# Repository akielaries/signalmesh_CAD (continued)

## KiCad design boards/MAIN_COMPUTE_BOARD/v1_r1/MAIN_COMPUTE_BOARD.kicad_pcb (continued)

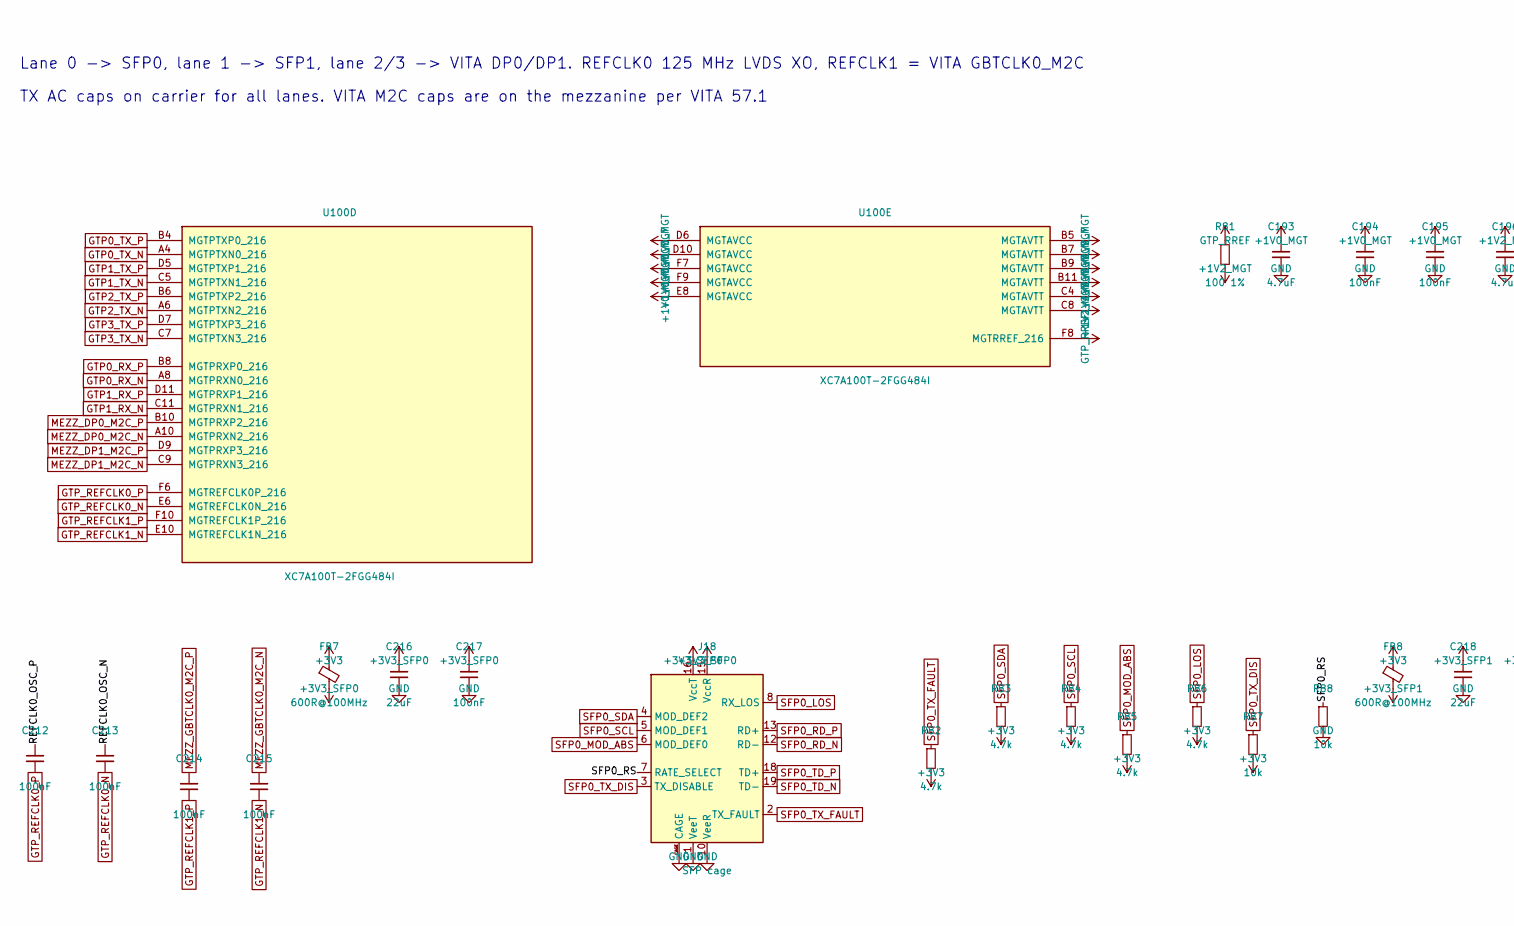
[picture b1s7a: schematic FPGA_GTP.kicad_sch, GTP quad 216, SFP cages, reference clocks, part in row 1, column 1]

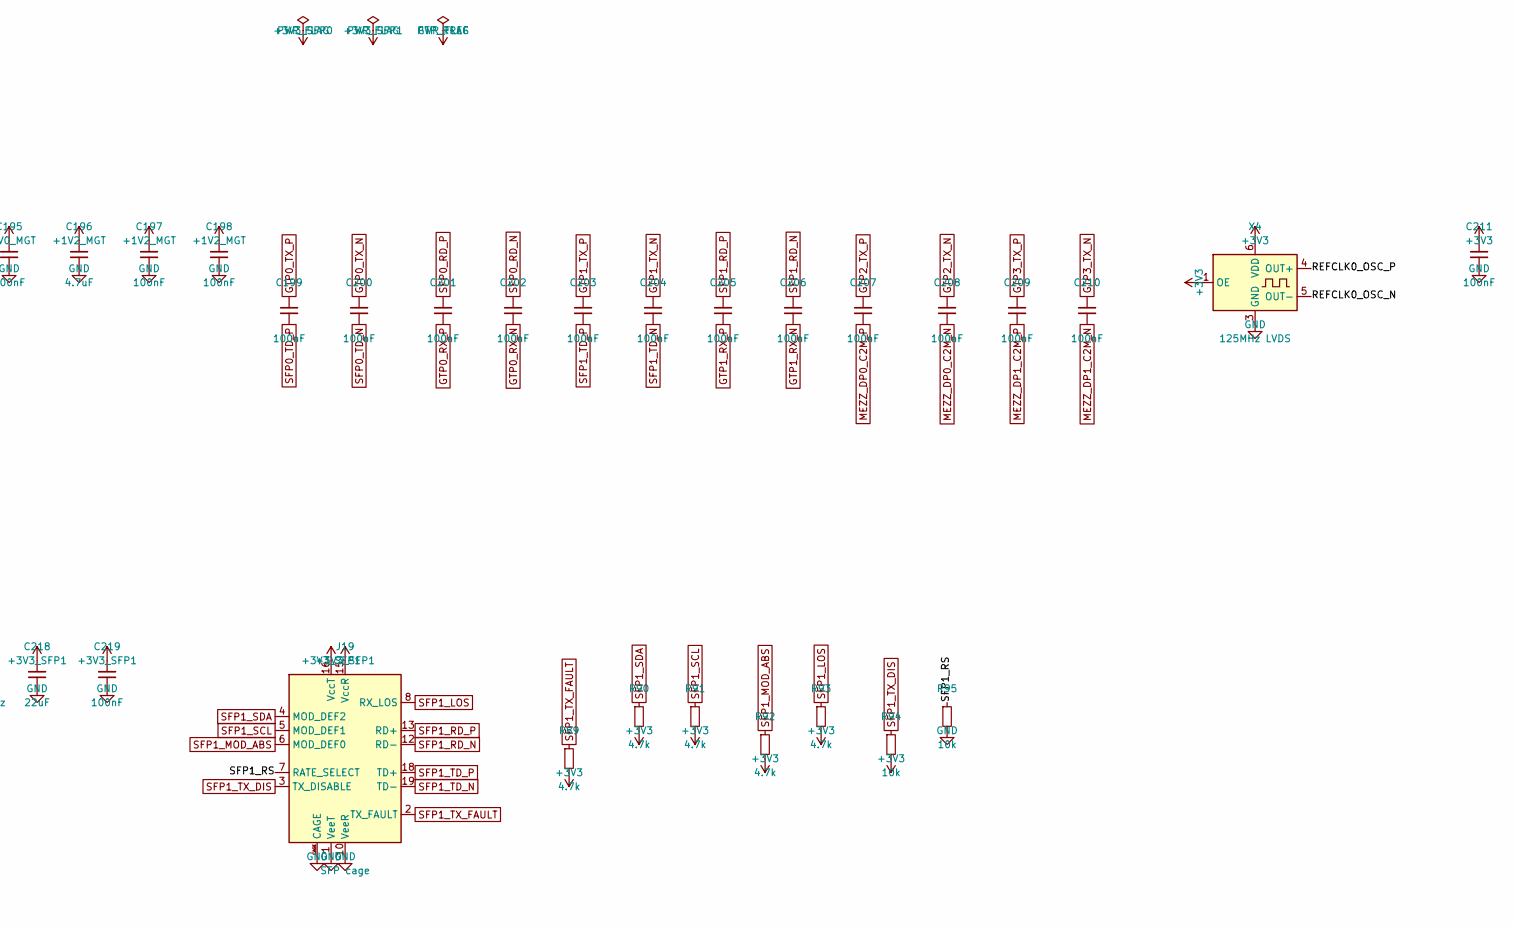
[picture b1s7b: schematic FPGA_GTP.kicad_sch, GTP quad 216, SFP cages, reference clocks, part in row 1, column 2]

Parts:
C193, C196: 4.7uF; C_0603_1608Metric
C194, C195, C197, C198, C211, C217, C219: 100nF; C_0402_1005Metric
C199, C200, C201, C202, C203, C204, C205, C206, C207, C208, C209, C210, C212, C213, C214, C215: 100nF; C_0201_0603Metric
C216, C218: 22uF; C_0805_2012Metric
FB7, FB8: 600R@100MHz; L_0603_1608Metric
J18, J19: SFP cage; Connector_SFP_and_Cage
R81: 100 1%; R_0402_1005Metric
R82, R83, R84, R85, R86, R89, R90, R91, R92, R93: 4.7k; R_0402_1005Metric
R87, R88, R94, R95: 10k; R_0402_1005Metric
U100: XC7A100T-2FGG484I; Xilinx_FGG484
X4: 125MHz LVDS; Oscillator_SMD_SiTime_PQFD-6L_3.2x2.5mm

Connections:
+1V0_MGT: C193.1, C194.1, C195.1, U100.D6 (MGTAVCC), U100.D10 (MGTAVCC), U100.E8 (MGTAVCC), U100.F7 (MGTAVCC), U100.F9 (MGTAVCC); also elsewhere on the board
+1V2_MGT: C196.1, C197.1, C198.1, R81.2, U100.B5 (MGTAVTT), U100.B7 (MGTAVTT), U100.B9 (MGTAVTT), U100.B11 (MGTAVTT), U100.C4 (MGTAVTT), U100.C8 (MGTAVTT); also elsewhere on the board
+3V3: C211.1, FB7.1, FB8.1, R82.2, R83.2, R84.2, R85.2, R86.2, R87.2, R89.2, R90.2, R91.2, R92.2, R93.2, R94.2, X4.1 (OE), X4.6 (VDD); also elsewhere on the board
+3V3_SFP0: C216.1, C217.1, FB7.2, J18.15 (VccR), J18.16 (VccT)
+3V3_SFP1: C218.1, C219.1, FB8.2, J19.15 (VccR), J19.16 (VccT)
/FPGA_GTP/REFCLK0_OSC_N: C213.1, X4.5 (OUT-)
/FPGA_GTP/REFCLK0_OSC_P: C212.1, X4.4 (OUT+)
/FPGA_GTP/SFP0_RS: J18.7 (RATE_SELECT), R88.1
/FPGA_GTP/SFP1_RS: J19.7 (RATE_SELECT), R95.1
GND: C193.2, C194.2, C195.2, C196.2, C197.2, C198.2, C211.2, C216.2, C217.2, C218.2, C219.2, J18.1 (VeeT), J18.9 (VeeR), J18.10 (VeeR), J18.11 (VeeR), J18.14 (VeeR), J18.17 (VeeT), J18.20 (VeeT), J18.CAGE, J19.1 (VeeT), J19.9 (VeeR), J19.10 (VeeR), J19.11 (VeeR), J19.14 (VeeR), J19.17 (VeeT), J19.20 (VeeT), J19.CAGE, R88.2, R95.2, X4.3 (GND); also elsewhere on the board
GTP0_RX_N: C202.2, U100.A8 (MGTPRXN0_216)
GTP0_RX_P: C201.2, U100.B8 (MGTPRXP0_216)
GTP0_TX_N: C200.1, U100.A4 (MGTPTXN0_216)
GTP0_TX_P: C199.1, U100.B4 (MGTPTXP0_216)
GTP1_RX_N: C206.2, U100.C11 (MGTPRXN1_216)
GTP1_RX_P: C205.2, U100.D11 (MGTPRXP1_216)
GTP1_TX_N: C204.1, U100.C5 (MGTPTXN1_216)
GTP1_TX_P: C203.1, U100.D5 (MGTPTXP1_216)
GTP2_TX_N: C208.1, U100.A6 (MGTPTXN2_216)
GTP2_TX_P: C207.1, U100.B6 (MGTPTXP2_216)
GTP3_TX_N: C210.1, U100.C7 (MGTPTXN3_216)
GTP3_TX_P: C209.1, U100.D7 (MGTPTXP3_216)
GTP_REFCLK0_N: C213.2, U100.E6 (MGTREFCLK0N_216)
GTP_REFCLK0_P: C212.2, U100.F6 (MGTREFCLK0P_216)
GTP_REFCLK1_N: C215.2, U100.E10 (MGTREFCLK1N_216)
GTP_REFCLK1_P: C214.2, U100.F10 (MGTREFCLK1P_216)
GTP_RREF: R81.1, U100.F8 (MGTRREF_216)
MEZZ_DP0_C2M_N: C208.2; also elsewhere on the board
MEZZ_DP0_C2M_P: C207.2; also elsewhere on the board
MEZZ_DP0_M2C_N: U100.A10 (MGTPRXN2_216); also elsewhere on the board
MEZZ_DP0_M2C_P: U100.B10 (MGTPRXP2_216); also elsewhere on the board
MEZZ_DP1_C2M_N: C210.2; also elsewhere on the board
MEZZ_DP1_C2M_P: C209.2; also elsewhere on the board
MEZZ_DP1_M2C_N: U100.C9 (MGTPRXN3_216); also elsewhere on the board
MEZZ_DP1_M2C_P: U100.D9 (MGTPRXP3_216); also elsewhere on the board
MEZZ_GBTCLK0_M2C_N: C215.1; also elsewhere on the board
MEZZ_GBTCLK0_M2C_P: C214.1; also elsewhere on the board
SFP0_LOS: J18.8 (RX_LOS), R86.1; also elsewhere on the board
SFP0_MOD_ABS: J18.6 (MOD_DEF0), R85.1; also elsewhere on the board
SFP0_RD_N: C202.1, J18.12 (RD-)
SFP0_RD_P: C201.1, J18.13 (RD+)
SFP0_SCL: J18.5 (MOD_DEF1), R84.1; also elsewhere on the board
SFP0_SDA: J18.4 (MOD_DEF2), R83.1; also elsewhere on the board
SFP0_TD_N: C200.2, J18.19 (TD-)
SFP0_TD_P: C199.2, J18.18 (TD+)
SFP0_TX_DIS: J18.3 (TX_DISABLE), R87.1; also elsewhere on the board
SFP0_TX_FAULT: J18.2 (TX_FAULT), R82.1; also elsewhere on the board
SFP1_LOS: J19.8 (RX_LOS), R93.1; also elsewhere on the board
SFP1_MOD_ABS: J19.6 (MOD_DEF0), R92.1; also elsewhere on the board
SFP1_RD_N: C206.1, J19.12 (RD-)
SFP1_RD_P: C205.1, J19.13 (RD+)
SFP1_SCL: J19.5 (MOD_DEF1), R91.1; also elsewhere on the board
SFP1_SDA: J19.4 (MOD_DEF2), R90.1; also elsewhere on the board
SFP1_TD_N: C204.2, J19.19 (TD-)
SFP1_TD_P: C203.2, J19.18 (TD+)
SFP1_TX_DIS: J19.3 (TX_DISABLE), R94.1; also elsewhere on the board
SFP1_TX_FAULT: J19.2 (TX_FAULT), R89.1; also elsewhere on the board

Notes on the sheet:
Lane 0 -> SFP0, lane 1 -> SFP1, lane 2/3 -> VITA DP0/DP1. REFCLK0 125 MHz LVDS XO, REFCLK1 = VITA GBTCLK0_M2C
TX AC caps on carrier for all lanes. VITA M2C caps are on the mezzanine per VITA 57.1

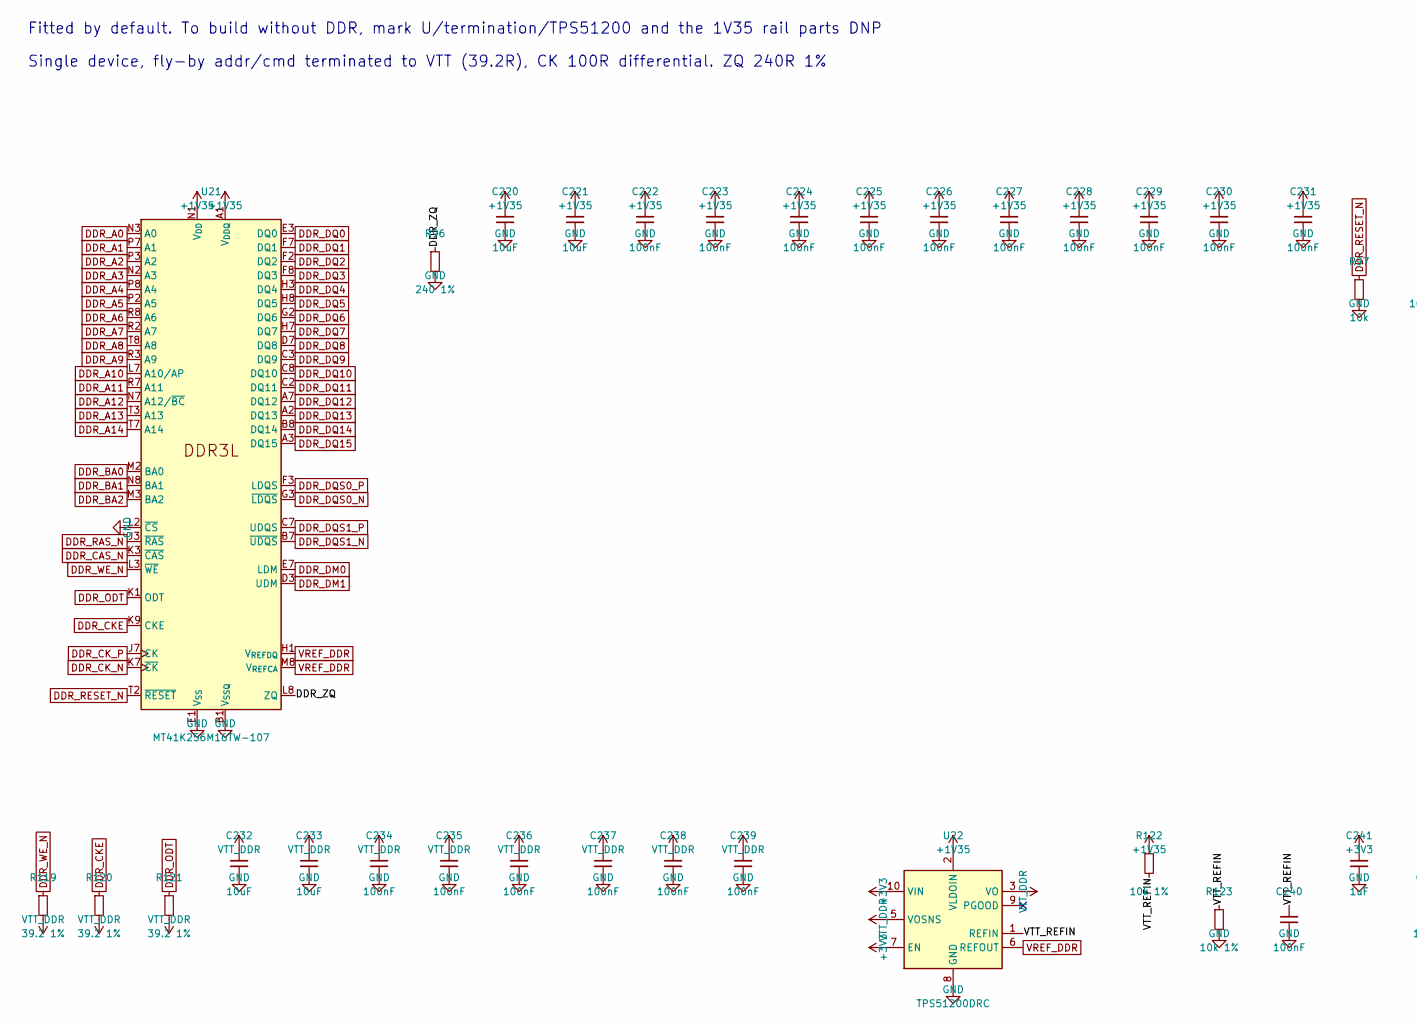
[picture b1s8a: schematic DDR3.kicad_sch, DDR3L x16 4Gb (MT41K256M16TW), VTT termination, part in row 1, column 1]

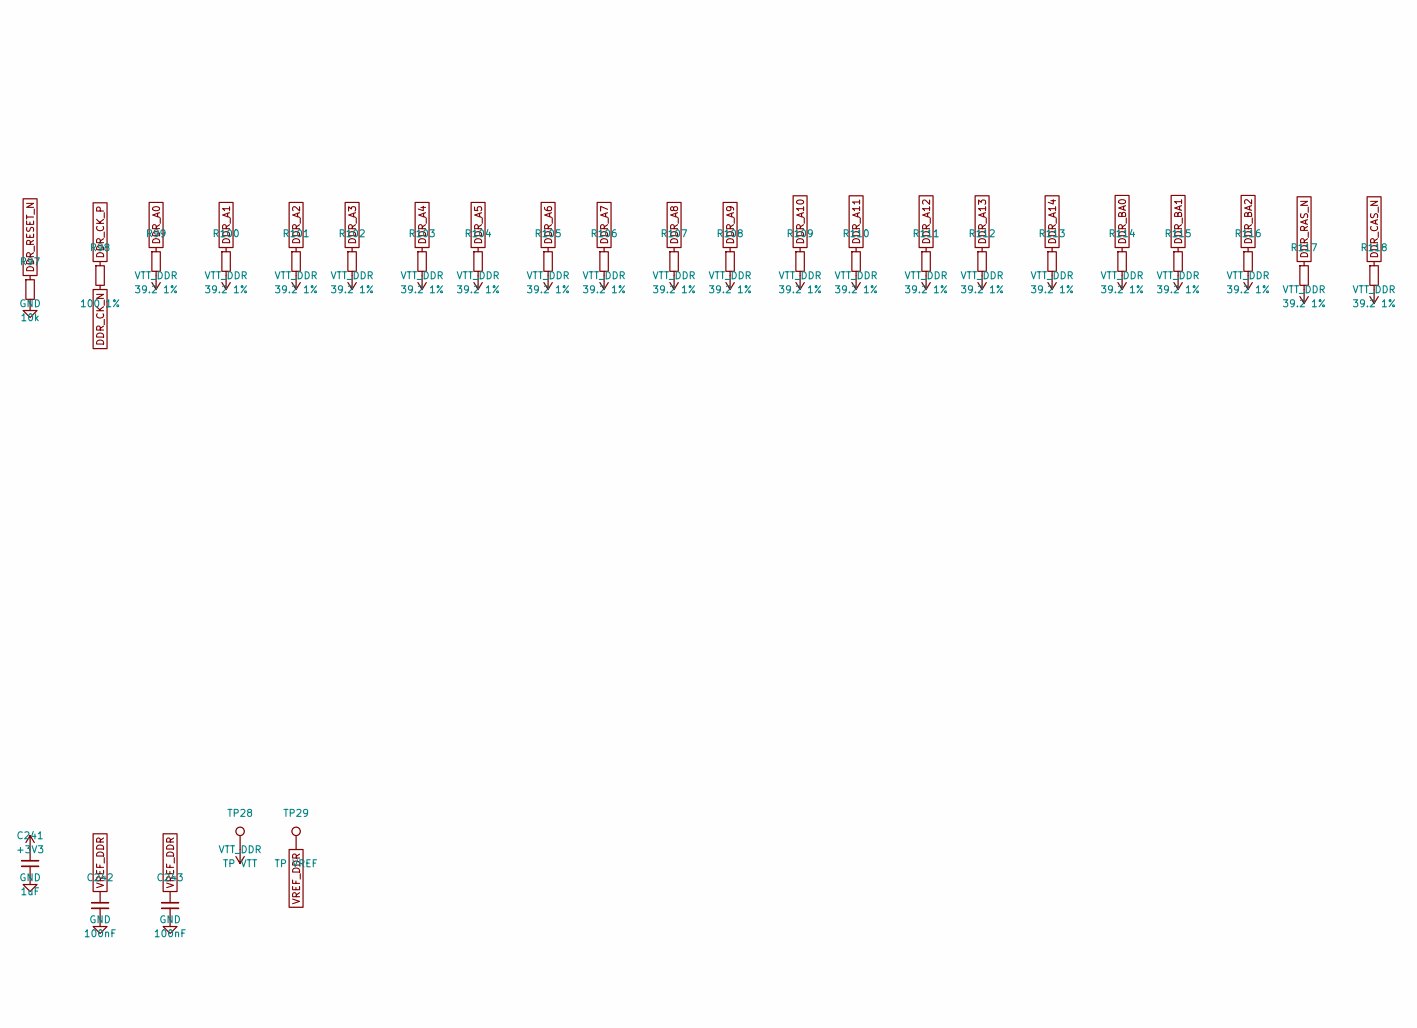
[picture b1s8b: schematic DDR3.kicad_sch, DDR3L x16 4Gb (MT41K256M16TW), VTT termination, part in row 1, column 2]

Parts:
C220, C221, C232, C233: 10uF; C_0805_2012Metric
C222, C223, C224, C225, C226, C227, C228, C229, C230, C231, C234, C235, C236, C237, C238, C239, C240, C242, C243: 100nF; C_0402_1005Metric
C241: 1uF; C_0402_1005Metric
R96: 240 1%; R_0402_1005Metric
R97: 10k; R_0402_1005Metric
R98: 100 1%; R_0402_1005Metric
R99, R100, R101, R102, R103, R104, R105, R106, R107, R108, R109, R110, R111, R112, R113, R114, R115, R116, R117, R118, R119, R120, R121: 39.2 1%; R_0402_1005Metric
R122, R123: 10k 1%; R_0402_1005Metric
TP28: TP VTT; TestPoint_Pad_D1.5mm
TP29: TP VREF; TestPoint_Pad_D1.5mm
U21: MT41K256M16TW-107; Micron_FBGA-96_8x14mm_Layout9x16_P0.8mm
U22: TPS51200DRC; VSON-10-1EP_3x3mm_P0.5mm_EP1.65x2.4mm

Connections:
+1V35: C220.1, C221.1, C222.1, C223.1, C224.1, C225.1, C226.1, C227.1, C228.1, C229.1, C230.1, C231.1, R122.1, U21.A1 (V_{DDQ}), U21.A8 (V_{DDQ}), U21.B2 (V_{DD}), U21.C1 (V_{DDQ}), U21.C9 (V_{DDQ}), U21.D2 (V_{DDQ}), U21.D9 (V_{DD}), U21.E9 (V_{DDQ}), U21.F1 (V_{DDQ}), U21.G7 (V_{DD}), U21.H2 (V_{DDQ}), U21.H9 (V_{DDQ}), U21.K2 (V_{DD}), U21.K8 (V_{DD}), U21.N1 (V_{DD}), U21.N9 (V_{DD}), U21.R1 (V_{DD}), U21.R9 (V_{DD}), U22.2 (VLDOIN); also elsewhere on the board
+3V3: C241.1, U22.7 (EN), U22.10 (VIN); also elsewhere on the board
/DDR3/DDR_ZQ: R96.1, U21.L8 (ZQ)
/DDR3/VTT_REFIN: C240.1, R122.2, R123.1, U22.1 (REFIN)
DDR_A0: R99.1, U21.N3 (A0); also elsewhere on the board
DDR_A1: R100.1, U21.P7 (A1); also elsewhere on the board
DDR_A2: R101.1, U21.P3 (A2); also elsewhere on the board
DDR_A3: R102.1, U21.N2 (A3); also elsewhere on the board
DDR_A4: R103.1, U21.P8 (A4); also elsewhere on the board
DDR_A5: R104.1, U21.P2 (A5); also elsewhere on the board
DDR_A6: R105.1, U21.R8 (A6); also elsewhere on the board
DDR_A7: R106.1, U21.R2 (A7); also elsewhere on the board
DDR_A8: R107.1, U21.T8 (A8); also elsewhere on the board
DDR_A9: R108.1, U21.R3 (A9); also elsewhere on the board
DDR_A10: R109.1, U21.L7 (A10/AP); also elsewhere on the board
DDR_A11: R110.1, U21.R7 (A11); also elsewhere on the board
DDR_A12: R111.1, U21.N7 (A12/~BC); also elsewhere on the board
DDR_A13: R112.1, U21.T3 (A13); also elsewhere on the board
DDR_A14: R113.1, U21.T7 (A14); also elsewhere on the board
DDR_BA0: R114.1, U21.M2 (BA0); also elsewhere on the board
DDR_BA1: R115.1, U21.N8 (BA1); also elsewhere on the board
DDR_BA2: R116.1, U21.M3 (BA2); also elsewhere on the board
DDR_CAS_N: R118.1, U21.K3 (~CAS); also elsewhere on the board
DDR_CKE: R120.1, U21.K9 (CKE); also elsewhere on the board
DDR_CK_N: R98.2, U21.K7 (~CK); also elsewhere on the board
DDR_CK_P: R98.1, U21.J7 (CK); also elsewhere on the board
DDR_DM0: U21.E7 (LDM); also elsewhere on the board
DDR_DM1: U21.D3 (UDM); also elsewhere on the board
DDR_DQ0: U21.E3 (DQ0); also elsewhere on the board
DDR_DQ1: U21.F7 (DQ1); also elsewhere on the board
DDR_DQ2: U21.F2 (DQ2); also elsewhere on the board
DDR_DQ3: U21.F8 (DQ3); also elsewhere on the board
DDR_DQ4: U21.H3 (DQ4); also elsewhere on the board
DDR_DQ5: U21.H8 (DQ5); also elsewhere on the board
DDR_DQ6: U21.G2 (DQ6); also elsewhere on the board
DDR_DQ7: U21.H7 (DQ7); also elsewhere on the board
DDR_DQ8: U21.D7 (DQ8); also elsewhere on the board
DDR_DQ9: U21.C3 (DQ9); also elsewhere on the board
DDR_DQ10: U21.C8 (DQ10); also elsewhere on the board
DDR_DQ11: U21.C2 (DQ11); also elsewhere on the board
DDR_DQ12: U21.A7 (DQ12); also elsewhere on the board
DDR_DQ13: U21.A2 (DQ13); also elsewhere on the board
DDR_DQ14: U21.B8 (DQ14); also elsewhere on the board
DDR_DQ15: U21.A3 (DQ15); also elsewhere on the board
DDR_DQS0_N: U21.G3 (~LDQS); also elsewhere on the board
DDR_DQS0_P: U21.F3 (LDQS); also elsewhere on the board
DDR_DQS1_N: U21.B7 (~UDQS); also elsewhere on the board
DDR_DQS1_P: U21.C7 (UDQS); also elsewhere on the board
DDR_ODT: R121.1, U21.K1 (ODT); also elsewhere on the board
DDR_RAS_N: R117.1, U21.J3 (~RAS); also elsewhere on the board
DDR_RESET_N: R97.1, U21.T2 (~RESET); also elsewhere on the board
DDR_WE_N: R119.1, U21.L3 (~WE); also elsewhere on the board
GND: C220.2, C221.2, C222.2, C223.2, C224.2, C225.2, C226.2, C227.2, C228.2, C229.2, C230.2, C231.2, C232.2, C233.2, C234.2, C235.2, C236.2, C237.2, C238.2, C239.2, C240.2, C241.2, C242.2, C243.2, R96.2, R97.2, R123.2, U21.A9 (V_{SS}), U21.B1 (V_{SSQ}), U21.B3 (V_{SS}), U21.B9 (V_{SSQ}), U21.D1 (V_{SSQ}), U21.D8 (V_{SSQ}), U21.E1 (V_{SS}), U21.E2 (V_{SSQ}), U21.E8 (V_{SSQ}), U21.F9 (V_{SSQ}), U21.G1 (V_{SSQ}), U21.G8 (V_{SS}), U21.G9 (V_{SSQ}), U21.J2 (V_{SS}), U21.J8 (V_{SS}), U21.L2 (~CS), U21.M1 (V_{SS}), U21.M9 (V_{SS}), U21.P1 (V_{SS}), U21.P9 (V_{SS}), U21.T1 (V_{SS}), U21.T9 (V_{SS}), U22.4 (GND), U22.8 (GND), U22.11 (GND); also elsewhere on the board
VREF_DDR: C242.1, C243.1, TP29.1, U21.H1 (V_{REFDQ}), U21.M8 (V_{REFCA}), U22.6 (REFOUT)
VTT_DDR: C232.1, C233.1, C234.1, C235.1, C236.1, C237.1, C238.1, C239.1, R99.2, R100.2, R101.2, R102.2, R103.2, R104.2, R105.2, R106.2, R107.2, R108.2, R109.2, R110.2, R111.2, R112.2, R113.2, R114.2, R115.2, R116.2, R117.2, R118.2, R119.2, R120.2, R121.2, TP28.1, U22.3 (VO), U22.5 (VOSNS)

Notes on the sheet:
Fitted by default. To build without DDR, mark U/termination/TPS51200 and the 1V35 rail parts DNP
Single device, fly-by addr/cmd terminated to VTT (39.2R), CK 100R differential. ZQ 240R 1%

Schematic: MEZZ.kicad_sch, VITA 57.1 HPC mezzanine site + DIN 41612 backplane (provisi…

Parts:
C244, C248: 47uF; C_1206_3216Metric
C245, C249: 10uF; C_0805_2012Metric
C246, C247, C250, C251: 100nF; C_0402_1005Metric
C252: 10uF 25V; C_0805_2012Metric
C253: 100nF 25V; C_0402_1005Metric
H5, H6: M2.5 VITA; MountingHole_2.7mm_M2.5_Pad_Via
J20: VITA57.1 HPC ASP-134486-01; Samtec_FMC_ASP-134486-01_10x40_P1.27mm_Vertical
J21: DIN41612 C 3x32 BACKPLANE; DIN41612_C_3x32_Male_Horizontal_THT
R124, R125: 10k; R_0402_1005Metric
R126: 100k; R_0402_1005Metric

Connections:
+3V3: J20.D32 (Pin_32), R124.2, R125.2; also elsewhere on the board
+3V3_MEZZ: C244.1, C245.1, C246.1, C247.1, J20.C39 (Pin_39), J20.D36 (Pin_36), J20.D38 (Pin_38), J20.D40 (Pin_40); also elsewhere on the board
+12V_JACK: J21.a1, J21.a2, J21.b1, J21.b2, J21.c1, J21.c2; also elsewhere on the board
+12V_MEZZ: C252.1, C253.1, J20.C35 (Pin_35), J20.C37 (Pin_37); also elsewhere on the board
BP_CANH: J21.c5; also elsewhere on the board
BP_CANL: J21.c6; also elsewhere on the board
BP_TDM_BCLK: J21.a7; also elsewhere on the board
BP_TDM_DIN: J21.a13; also elsewhere on the board
BP_TDM_DOUT: J21.a11; also elsewhere on the board
BP_TDM_FS: J21.a9; also elsewhere on the board
BP_TDM_MCLK: J21.a5; also elsewhere on the board
GND: C244.2, C245.2, C246.2, C247.2, C248.2, C249.2, C250.2, C251.2, C252.2, C253.2, H5.1, H6.1, J20.A1 (Pin_1), J20.A4 (Pin_4), J20.A5 (Pin_5), J20.A8 (Pin_8), J20.A9 (Pin_9), J20.A12 (Pin_12), J20.A13 (Pin_13), J20.A16 (Pin_16), J20.A17 (Pin_17), J20.A20 (Pin_20), J20.A21 (Pin_21), J20.A24 (Pin_24), J20.A25 (Pin_25), J20.A28 (Pin_28), J20.A29 (Pin_29), J20.A32 (Pin_32), J20.A33 (Pin_33), J20.A36 (Pin_36), J20.A37 (Pin_37), J20.A40 (Pin_40), J20.B2 (Pin_2), J20.B3 (Pin_3), J20.B6 (Pin_6), J20.B7 (Pin_7), J20.B10 (Pin_10), J20.B11 (Pin_11), J20.B14 (Pin_14), J20.B15 (Pin_15), J20.B18 (Pin_18), J20.B19 (Pin_19), J20.B22 (Pin_22), J20.B23 (Pin_23), J20.B26 (Pin_26), J20.B27 (Pin_27), J20.B30 (Pin_30), J20.B31 (Pin_31), J20.B34 (Pin_34), J20.B35 (Pin_35), J20.B38 (Pin_38), J20.B39 (Pin_39), J20.C1 (Pin_1), J20.C4 (Pin_4), J20.C5 (Pin_5), J20.C8 (Pin_8), J20.C9 (Pin_9), J20.C12 (Pin_12), J20.C13 (Pin_13), J20.C16 (Pin_16), J20.C17 (Pin_17), J20.C20 (Pin_20), J20.C21 (Pin_21), J20.C24 (Pin_24), J20.C25 (Pin_25), J20.C28 (Pin_28), J20.C29 (Pin_29), J20.C32 (Pin_32), J20.C33 (Pin_33), J20.C34 (Pin_34), J20.C36 (Pin_36), J20.C38 (Pin_38), J20.C40 (Pin_40), J20.D2 (Pin_2), J20.D3 (Pin_3), J20.D6 (Pin_6), J20.D7 (Pin_7), J20.D10 (Pin_10), J20.D13 (Pin_13), J20.D16 (Pin_16), J20.D19 (Pin_19), J20.D22 (Pin_22), J20.D25 (Pin_25), J20.D28 (Pin_28), J20.D35 (Pin_35), J20.D37 (Pin_37), J20.D39 (Pin_39), J20.E1 (Pin_1), J20.E4 (Pin_4), J20.E5 (Pin_5), J20.E8 (Pin_8), J20.E11 (Pin_11), J20.E14 (Pin_14), J20.E17 (Pin_17), J20.E20 (Pin_20), J20.E23 (Pin_23), J20.E26 (Pin_26), J20.E29 (Pin_29), J20.E32 (Pin_32), J20.E35 (Pin_35), J20.E38 (Pin_38), J20.E40 (Pin_40), J20.F2 (Pin_2), J20.F3 (Pin_3), J20.F6 (Pin_6), J20.F9 (Pin_9), J20.F12 (Pin_12), J20.F15 (Pin_15), J20.F18 (Pin_18), J20.F21 (Pin_21), J20.F24 (Pin_24), J20.F27 (Pin_27), J20.F30 (Pin_30), J20.F33 (Pin_33), J20.F36 (Pin_36), J20.F39 (Pin_39), J20.G1 (Pin_1), J20.G4 (Pin_4), J20.G5 (Pin_5), J20.G8 (Pin_8), J20.G11 (Pin_11), J20.G14 (Pin_14), J20.G17 (Pin_17), J20.G20 (Pin_20), J20.G23 (Pin_23), J20.G26 (Pin_26), J20.G29 (Pin_29), J20.G32 (Pin_32), J20.G35 (Pin_35), J20.G38 (Pin_38), J20.G40 (Pin_40), J20.H3 (Pin_3), J20.H6 (Pin_6), J20.H9 (Pin_9), J20.H12 (Pin_12), J20.H15 (Pin_15), J20.H18 (Pin_18), J20.H21 (Pin_21), J20.H24 (Pin_24), J20.H27 (Pin_27), J20.H30 (Pin_30), J20.H33 (Pin_33), J20.H36 (Pin_36), J20.H39 (Pin_39), J20.J1 (Pin_1), J20.J4 (Pin_4), J20.J5 (Pin_5), J20.J8 (Pin_8), J20.J11 (Pin_11), J20.J14 (Pin_14), J20.J17 (Pin_17), J20.J20 (Pin_20), J20.J23 (Pin_23), J20.J26 (Pin_26), J20.J29 (Pin_29), J20.J32 (Pin_32), J20.J35 (Pin_35), J20.J38 (Pin_38), J20.J40 (Pin_40), J20.K2 (Pin_2), J20.K3 (Pin_3), J20.K6 (Pin_6), J20.K9 (Pin_9), J20.K12 (Pin_12), J20.K15 (Pin_15), J20.K18 (Pin_18), J20.K21 (Pin_21), J20.K24 (Pin_24), J20.K27 (Pin_27), J20.K30 (Pin_30), J20.K33 (Pin_33), J20.K36 (Pin_36), J20.K39 (Pin_39), J21.a3, J21.a32, J21.b3, J21.b4, J21.b6, J21.b8, J21.b10, J21.b12, J21.b14, J21.b16, J21.b18, J21.b20, J21.b22, J21.b24, J21.b26, J21.b28, J21.b30, J21.b32, J21.c3, J21.c32, R126.2; also elsewhere on the board
I2C1_SCL: J20.C30 (Pin_30); also elsewhere on the board
I2C1_SDA: J20.C31 (Pin_31); also elsewhere on the board
MEZZ_CLK0_M2C_N: J20.H5 (Pin_5); also elsewhere on the board
MEZZ_CLK0_M2C_P: J20.H4 (Pin_4); also elsewhere on the board
MEZZ_CLK1_M2C_N: J20.G3 (Pin_3); also elsewhere on the board
MEZZ_CLK1_M2C_P: J20.G2 (Pin_2); also elsewhere on the board
MEZZ_DP0_C2M_N: J20.C3 (Pin_3); also elsewhere on the board
MEZZ_DP0_C2M_P: J20.C2 (Pin_2); also elsewhere on the board
MEZZ_DP0_M2C_N: J20.C7 (Pin_7); also elsewhere on the board
MEZZ_DP0_M2C_P: J20.C6 (Pin_6); also elsewhere on the board
MEZZ_DP1_C2M_N: J20.A23 (Pin_23); also elsewhere on the board
MEZZ_DP1_C2M_P: J20.A22 (Pin_22); also elsewhere on the board
MEZZ_DP1_M2C_N: J20.A3 (Pin_3); also elsewhere on the board
MEZZ_DP1_M2C_P: J20.A2 (Pin_2); also elsewhere on the board
MEZZ_GBTCLK0_M2C_N: J20.D5 (Pin_5); also elsewhere on the board
MEZZ_GBTCLK0_M2C_P: J20.D4 (Pin_4); also elsewhere on the board
MEZZ_LA00_CC_N: J20.G7 (Pin_7); also elsewhere on the board
MEZZ_LA00_CC_P: J20.G6 (Pin_6); also elsewhere on the board
MEZZ_LA01_CC_N: J20.D9 (Pin_9); also elsewhere on the board
MEZZ_LA01_CC_P: J20.D8 (Pin_8); also elsewhere on the board
MEZZ_LA02_N: J20.H8 (Pin_8); also elsewhere on the board
MEZZ_LA02_P: J20.H7 (Pin_7); also elsewhere on the board
MEZZ_LA03_N: J20.G10 (Pin_10); also elsewhere on the board
MEZZ_LA03_P: J20.G9 (Pin_9); also elsewhere on the board
MEZZ_LA04_N: J20.H11 (Pin_11); also elsewhere on the board
MEZZ_LA04_P: J20.H10 (Pin_10); also elsewhere on the board
MEZZ_LA05_N: J20.D12 (Pin_12); also elsewhere on the board
MEZZ_LA05_P: J20.D11 (Pin_11); also elsewhere on the board
MEZZ_LA06_N: J20.C11 (Pin_11); also elsewhere on the board
MEZZ_LA06_P: J20.C10 (Pin_10); also elsewhere on the board
MEZZ_LA07_N: J20.H14 (Pin_14); also elsewhere on the board
MEZZ_LA07_P: J20.H13 (Pin_13); also elsewhere on the board
MEZZ_LA08_N: J20.G13 (Pin_13); also elsewhere on the board
MEZZ_LA08_P: J20.G12 (Pin_12); also elsewhere on the board
MEZZ_LA09_N: J20.D15 (Pin_15); also elsewhere on the board
MEZZ_LA09_P: J20.D14 (Pin_14); also elsewhere on the board
MEZZ_LA10_N: J20.C15 (Pin_15); also elsewhere on the board
MEZZ_LA10_P: J20.C14 (Pin_14); also elsewhere on the board
MEZZ_LA11_N: J20.H17 (Pin_17); also elsewhere on the board
MEZZ_LA11_P: J20.H16 (Pin_16); also elsewhere on the board
MEZZ_LA12_N: J20.G16 (Pin_16); also elsewhere on the board
MEZZ_LA12_P: J20.G15 (Pin_15); also elsewhere on the board
MEZZ_LA13_N: J20.D18 (Pin_18); also elsewhere on the board
MEZZ_LA13_P: J20.D17 (Pin_17); also elsewhere on the board
MEZZ_LA14_N: J20.C19 (Pin_19); also elsewhere on the board
MEZZ_LA14_P: J20.C18 (Pin_18); also elsewhere on the board
MEZZ_LA15_N: J20.H20 (Pin_20); also elsewhere on the board
MEZZ_LA15_P: J20.H19 (Pin_19); also elsewhere on the board
MEZZ_LA16_N: J20.G19 (Pin_19); also elsewhere on the board
MEZZ_LA16_P: J20.G18 (Pin_18); also elsewhere on the board
MEZZ_LA17_CC_N: J20.D21 (Pin_21); also elsewhere on the board
MEZZ_LA17_CC_P: J20.D20 (Pin_20); also elsewhere on the board
MEZZ_LA18_CC_N: J20.C23 (Pin_23); also elsewhere on the board
MEZZ_LA18_CC_P: J20.C22 (Pin_22); also elsewhere on the board
MEZZ_LA19_N: J20.H23 (Pin_23); also elsewhere on the board
MEZZ_LA19_P: J20.H22 (Pin_22); also elsewhere on the board
MEZZ_LA20_N: J20.G22 (Pin_22); also elsewhere on the board
MEZZ_LA20_P: J20.G21 (Pin_21); also elsewhere on the board
MEZZ_LA21_N: J20.H26 (Pin_26); also elsewhere on the board
MEZZ_LA21_P: J20.H25 (Pin_25); also elsewhere on the board
MEZZ_LA22_N: J20.G25 (Pin_25); also elsewhere on the board
MEZZ_LA22_P: J20.G24 (Pin_24); also elsewhere on the board
MEZZ_LA23_N: J20.D24 (Pin_24); also elsewhere on the board
MEZZ_LA23_P: J20.D23 (Pin_23); also elsewhere on the board
MEZZ_LA24_N: J20.H29 (Pin_29); also elsewhere on the board
MEZZ_LA24_P: J20.H28 (Pin_28); also elsewhere on the board
MEZZ_LA25_N: J20.G28 (Pin_28); also elsewhere on the board
MEZZ_LA25_P: J20.G27 (Pin_27); also elsewhere on the board
MEZZ_LA26_N: J20.D27 (Pin_27); also elsewhere on the board
MEZZ_LA26_P: J20.D26 (Pin_26); also elsewhere on the board
MEZZ_LA27_N: J20.C27 (Pin_27); also elsewhere on the board
MEZZ_LA27_P: J20.C26 (Pin_26); also elsewhere on the board
MEZZ_LA28_N: J20.H32 (Pin_32); also elsewhere on the board
MEZZ_LA28_P: J20.H31 (Pin_31); also elsewhere on the board
MEZZ_LA29_N: J20.G31 (Pin_31); also elsewhere on the board
MEZZ_LA29_P: J20.G30 (Pin_30); also elsewhere on the board
MEZZ_LA30_N: J20.H35 (Pin_35); also elsewhere on the board
MEZZ_LA30_P: J20.H34 (Pin_34); also elsewhere on the board
MEZZ_LA31_N: J20.G34 (Pin_34); also elsewhere on the board
MEZZ_LA31_P: J20.G33 (Pin_33); also elsewhere on the board
MEZZ_LA32_N: J20.H38 (Pin_38); also elsewhere on the board
MEZZ_LA32_P: J20.H37 (Pin_37); also elsewhere on the board
MEZZ_LA33_N: J20.G37 (Pin_37); also elsewhere on the board
MEZZ_LA33_P: J20.G36 (Pin_36); also elsewhere on the board
MEZZ_PG_C2M: J20.D1 (Pin_1), R126.1; also elsewhere on the board
MEZZ_PG_M2C: J20.F1 (Pin_1), R125.1; also elsewhere on the board
MEZZ_PRSNT_L: J20.H2 (Pin_2), R124.1; also elsewhere on the board
VADJ: C248.1, C249.1, C250.1, C251.1, J20.E39 (Pin_39), J20.F40 (Pin_40), J20.G39 (Pin_39), J20.H40 (Pin_40); also elsewhere on the board

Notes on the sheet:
VITA 57.1 HPC connector, LPC-compatible. Routed: LA00-LA33, CLK0/1_M2C, GBTCLK0_M2C, DP0-DP1, I2C, PG/PRSNT
VADJ set by STM32 after reading mezzanine EEPROM (I2C1 0x50, GA=00). HA/HB/DP2-9 not connected
DIN 41612 3x32 backplane pinout is PROVISIONAL (12V in/out shared with barrel jack, TDM audio bus, CAN). Use one 12V source at a time
DIN a28/c28 = -12V and a30/c30 = +5V are reserved for other cards and left unconnected here (do not back-feed this board)

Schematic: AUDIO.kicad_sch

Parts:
C254, C264, C268, C269, C272: 0.1uF; C_0402_1005Metric
C255, C256, C257, C258, C259, C260, C263, C266, C270, C273: 10uF; C_0805_2012Metric
C261, C271: 2.7nF; C_0402_1005Metric
C262, C265: 47pF; C_0402_1005Metric
C267: 100uF; C_0805_2012Metric
J22: ACM_DAC_L; U.FL_Hirose_U.FL-R-SMT-1_Vertical
J23: DAC_L_PRB; U.FL_Hirose_U.FL-R-SMT-1_Vertical
J24: ACM_DAC_R; U.FL_Hirose_U.FL-R-SMT-1_Vertical
R127, R137: 1k; R_0201_0603Metric; DigiKey_Part_Number 311-10.0KCRCT-ND
R128, R131: 47k; R_0201_0603Metric; DigiKey_Part_Number 311-10.0KCRCT-ND
R129, R130, R132, R138: 22; R_0201_0603Metric; DigiKey_Part_Number 311-10.0KCRCT-ND
R133, R140: 2k; R_0201_0603Metric; DigiKey_Part_Number 311-10.0KCRCT-ND
R134, R139: 560; R_0201_0603Metric; DigiKey_Part_Number 311-10.0KCRCT-ND
R135, R136: 100; R_0201_0603Metric; DigiKey_Part_Number 311-10.0KCRCT-ND
TP30: DAC_L; TestPoint_Pad_D1.0mm
U23: LM2662M; SOIC-8_3.9x4.9mm_P1.27mm
U24: CS4344; TSSOP-10_3x3mm_P0.5mm
U25: OPA1656ID; SOIC-8_3.9x4.9mm_P1.27mm

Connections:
+3V3_AUD: C258.2, U24.9 (VA); also elsewhere on the board
+5V_AUD: C270.2, U23.1 (BOOST), U23.8 (V+), U25.8 (V+); also elsewhere on the board
-5V: C257.2, C267.1, U23.5 (VOUT), U25.4 (V-)
AUD_DAC_LRCK: R130.1; also elsewhere on the board
AUD_DAC_MCLK: R132.1; also elsewhere on the board
AUD_DAC_SCLK: R138.1; also elsewhere on the board
AUD_DAC_SDIN: R129.1; also elsewhere on the board
GND: C254.1, C261.1, C262.1, C264.1, C265.1, C267.2, C268.1, C269.1, C271.1, C272.1, J22.2 (Ext), J23.2 (Ext), J24.2 (Ext), R128.2, R131.2, R133.2, R140.2, U23.3 (GND), U24.8 (GND); also elsewhere on the board
unnamed: C254.2, C258.1
unnamed: C255.2, C261.2, R134.2
unnamed: C256.1, R135.1
unnamed: C256.2, R127.1, U25.1
unnamed: C257.1, C268.2
unnamed: C260.1, C269.2
unnamed: C263.2, C271.2, R139.2
unnamed: C264.2, C270.1
unnamed: C266.1, R136.1
unnamed: C266.2, R137.1, U25.7
unnamed: C272.2, C273.1
unnamed: C265.2, J22.1 (In), R135.2
unnamed: C262.2, J24.1 (In), R136.2
unnamed: C259.1, U23.2 (CAP+)
unnamed: C259.2, U23.4 (CAP-)
unnamed: R139.1, U24.7 (AOUTL)
unnamed: R134.1, U24.10 (AOUTR)
unnamed: C273.2, U24.6 (FILT+)
unnamed: R130.2, U24.3 (LRCK)
unnamed: R132.2, U24.4 (MCLK)
unnamed: R129.2, U24.1 (SDIN)
unnamed: C260.2, U24.5 (VQ)
unnamed: R138.2, U24.2 (~DEM/SCLK)
unnamed: C263.1, R131.1, U25.3 (+)
unnamed: R127.2, R140.1, U25.2 (-)
unnamed: C255.1, R128.1, U25.5 (+)
unnamed: R133.1, R137.2, U25.6 (-)
STM32_DAC1_OUT1: J23.1 (In), TP30.1; also elsewhere on the board

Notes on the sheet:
AUDIO OUT
Two DAC output circuits\n1. STM32 built-in 12-bit DAC\n2. FPGA -> CS4344 24-bit DAC

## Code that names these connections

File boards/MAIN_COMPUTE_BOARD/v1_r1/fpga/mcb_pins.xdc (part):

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set_property BITSTREAM.CONFIG.CONFIGRATE 50 [current_design]

# bank 13, VCCO 3.3 V
set_property -dict {PACKAGE_PIN AA10 IOSTANDARD LVCMOS33    } [get_ports aud_dac_lrck]
set_property -dict {PACKAGE_PIN AA9  IOSTANDARD LVCMOS33    } [get_ports aud_dac_mclk]
set_property -dict {PACKAGE_PIN AA11 IOSTANDARD LVCMOS33    } [get_ports aud_dac_sclk]
set_property -dict {PACKAGE_PIN W10  IOSTANDARD LVCMOS33    } [get_ports aud_dac_sdin]
set_property -dict {PACKAGE_PIN Y17  IOSTANDARD LVCMOS33    } [get_ports pmoda_io1]
set_property -dict {PACKAGE_PIN AA16 IOSTANDARD LVCMOS33    } [get_ports pmoda_io2]
set_property -dict {PACKAGE_PIN Y16  IOSTANDARD LVCMOS33    } [get_ports pmoda_io3]
set_property -dict {PACKAGE_PIN AB17 IOSTANDARD LVCMOS33    } [get_ports pmoda_io4]
set_property -dict {PACKAGE_PIN AB16 IOSTANDARD LVCMOS33    } [get_ports pmoda_io5]
set_property -dict {PACKAGE_PIN AB13 IOSTANDARD LVCMOS33    } [get_ports pmoda_io6]
set_property -dict {PACKAGE_PIN AA13 IOSTANDARD LVCMOS33    } [get_ports pmoda_io7]
set_property -dict {PACKAGE_PIN AB15 IOSTANDARD LVCMOS33    } [get_ports pmoda_io8]
set_property -dict {PACKAGE_PIN AA15 IOSTANDARD LVCMOS33    } [get_ports pmodb_io1]
set_property -dict {PACKAGE_PIN AA14 IOSTANDARD LVCMOS33    } [get_ports pmodb_io2]
set_property -dict {PACKAGE_PIN Y13  IOSTANDARD LVCMOS33    } [get_ports pmodb_io3]
set_property -dict {PACKAGE_PIN Y14  IOSTANDARD LVCMOS33    } [get_ports pmodb_io4]
set_property -dict {PACKAGE_PIN W14  IOSTANDARD LVCMOS33    } [get_ports pmodb_io5]
set_property -dict {PACKAGE_PIN AB12 IOSTANDARD LVCMOS33    } [get_ports pmodb_io6]
set_property -dict {PACKAGE_PIN AB11 IOSTANDARD LVCMOS33    } [get_ports pmodb_io7]
set_property -dict {PACKAGE_PIN AB10 IOSTANDARD LVCMOS33    } [get_ports pmodb_io8]
set_property -dict {PACKAGE_PIN Y12  IOSTANDARD LVCMOS33    } [get_ports sfp0_los]
set_property -dict {PACKAGE_PIN V10  IOSTANDARD LVCMOS33    } [get_ports sfp0_mod_abs]
set_property -dict {PACKAGE_PIN W11  IOSTANDARD LVCMOS33    } [get_ports sfp0_scl]
set_property -dict {PACKAGE_PIN V14  IOSTANDARD LVCMOS33    } [get_ports sfp0_sda]
set_property -dict {PACKAGE_PIN W12  IOSTANDARD LVCMOS33    } [get_ports sfp0_tx_dis]
set_property -dict {PACKAGE_PIN Y11  IOSTANDARD LVCMOS33    } [get_ports sfp0_tx_fault]
set_property -dict {PACKAGE_PIN V15  IOSTANDARD LVCMOS33    } [get_ports sfp1_los]
set_property -dict {PACKAGE_PIN V13  IOSTANDARD LVCMOS33    } [get_ports sfp1_mod_abs]
set_property -dict {PACKAGE_PIN T14  IOSTANDARD LVCMOS33    } [get_ports sfp1_scl]
set_property -dict {PACKAGE_PIN W16  IOSTANDARD LVCMOS33    } [get_ports sfp1_sda]
set_property -dict {PACKAGE_PIN T15  IOSTANDARD LVCMOS33    } [get_ports sfp1_tx_dis]
set_property -dict {PACKAGE_PIN U15  IOSTANDARD LVCMOS33    } [get_ports sfp1_tx_fault]

# bank 14, VCCO 3.3 V
set_property -dict {PACKAGE_PIN W19  IOSTANDARD LVCMOS33    } [get_ports fmc_clk]
set_property -dict {PACKAGE_PIN P22  IOSTANDARD LVCMOS33    } [get_ports fmc_d0]
set_property -dict {PACKAGE_PIN R22  IOSTANDARD LVCMOS33    } [get_ports fmc_d1]
set_property -dict {PACKAGE_PIN W22  IOSTANDARD LVCMOS33    } [get_ports fmc_d10]
set_property -dict {PACKAGE_PIN AA20 IOSTANDARD LVCMOS33    } [get_ports fmc_d11]
set_property -dict {PACKAGE_PIN AA21 IOSTANDARD LVCMOS33    } [get_ports fmc_d12]
set_property -dict {PACKAGE_PIN Y22  IOSTANDARD LVCMOS33    } [get_ports fmc_d13]
set_property -dict {PACKAGE_PIN AB21 IOSTANDARD LVCMOS33    } [get_ports fmc_d14]
set_property -dict {PACKAGE_PIN AB22 IOSTANDARD LVCMOS33    } [get_ports fmc_d15]
set_property -dict {PACKAGE_PIN AB18 IOSTANDARD LVCMOS33    } [get_ports fmc_d16]
set_property -dict {PACKAGE_PIN AA18 IOSTANDARD LVCMOS33    } [get_ports fmc_d17]
set_property -dict {PACKAGE_PIN W17  IOSTANDARD LVCMOS33    } [get_ports fmc_d18]
set_property -dict {PACKAGE_PIN U17  IOSTANDARD LVCMOS33    } [get_ports fmc_d19]
set_property -dict {PACKAGE_PIN P21  IOSTANDARD LVCMOS33    } [get_ports fmc_d2]
set_property -dict {PACKAGE_PIN U18  IOSTANDARD LVCMOS33    } [get_ports fmc_d20]
set_property -dict {PACKAGE_PIN R17  IOSTANDARD LVCMOS33    } [get_ports fmc_d21]
set_property -dict {PACKAGE_PIN R16  IOSTANDARD LVCMOS33    } [get_ports fmc_d22]
set_property -dict {PACKAGE_PIN R14  IOSTANDARD LVCMOS33    } [get_ports fmc_d23]
set_property -dict {PACKAGE_PIN P17  IOSTANDARD LVCMOS33    } [get_ports fmc_d24]
set_property -dict {PACKAGE_PIN P16  IOSTANDARD LVCMOS33    } [get_ports fmc_d25]
set_property -dict {PACKAGE_PIN P15  IOSTANDARD LVCMOS33    } [get_ports fmc_d26]
set_property -dict {PACKAGE_PIN P14  IOSTANDARD LVCMOS33    } [get_ports fmc_d27]
set_property -dict {PACKAGE_PIN N14  IOSTANDARD LVCMOS33    } [get_ports fmc_d28]
set_property -dict {PACKAGE_PIN N13  IOSTANDARD LVCMOS33    } [get_ports fmc_d29]
set_property -dict {PACKAGE_PIN R21  IOSTANDARD LVCMOS33    } [get_ports fmc_d3]
set_property -dict {PACKAGE_PIN R18  IOSTANDARD LVCMOS33    } [get_ports fmc_d30]
set_property -dict {PACKAGE_PIN T18  IOSTANDARD LVCMOS33    } [get_ports fmc_d31]
set_property -dict {PACKAGE_PIN T21  IOSTANDARD LVCMOS33    } [get_ports fmc_d4]
set_property -dict {PACKAGE_PIN U21  IOSTANDARD LVCMOS33    } [get_ports fmc_d5]
set_property -dict {PACKAGE_PIN P19  IOSTANDARD LVCMOS33    } [get_ports fmc_d6]
set_property -dict {PACKAGE_PIN R19  IOSTANDARD LVCMOS33    } [get_ports fmc_d7]
set_property -dict {PACKAGE_PIN T20  IOSTANDARD LVCMOS33    } [get_ports fmc_d8]
set_property -dict {PACKAGE_PIN W21  IOSTANDARD LVCMOS33    } [get_ports fmc_d9]
set_property -dict {PACKAGE_PIN T19  IOSTANDARD LVCMOS33    } [get_ports fmc_nbl0]
set_property -dict {PACKAGE_PIN P20  IOSTANDARD LVCMOS33    } [get_ports fmc_nbl1]
set_property -dict {PACKAGE_PIN N17  IOSTANDARD LVCMOS33    } [get_ports fmc_nbl2]
set_property -dict {PACKAGE_PIN N15  IOSTANDARD LVCMOS33    } [get_ports fmc_nbl3]
set_property -dict {PACKAGE_PIN U20  IOSTANDARD LVCMOS33    } [get_ports fmc_ne1]
set_property -dict {PACKAGE_PIN Y21  IOSTANDARD LVCMOS33    } [get_ports fmc_noe]
set_property -dict {PACKAGE_PIN V20  IOSTANDARD LVCMOS33    } [get_ports fmc_nwait]
set_property -dict {PACKAGE_PIN V22  IOSTANDARD LVCMOS33    } [get_ports fmc_nwe]
set_property -dict {PACKAGE_PIN V17  IOSTANDARD LVCMOS33    } [get_ports fpga_csi_b]
set_property -dict {PACKAGE_PIN AB20 IOSTANDARD LVCMOS33    } [get_ports fpga_irq0]
set_property -dict {PACKAGE_PIN V19  IOSTANDARD LVCMOS33    } [get_ports fpga_irq1]
set_property -dict {PACKAGE_PIN V18  IOSTANDARD LVCMOS33    } [get_ports fpga_irq2]
set_property -dict {PACKAGE_PIN U22  IOSTANDARD LVCMOS33    } [get_ports fpga_pudc_b]
set_property -dict {PACKAGE_PIN AA19 IOSTANDARD LVCMOS33    } [get_ports fpga_rdwr_b]
set_property -dict {PACKAGE_PIN W20  IOSTANDARD LVCMOS33    } [get_ports fpga_rst_n]
set_property -dict {PACKAGE_PIN Y19  IOSTANDARD LVCMOS33    } [get_ports mcu_uart_rx]
set_property -dict {PACKAGE_PIN Y18  IOSTANDARD LVCMOS33    } [get_ports mcu_uart_tx]

# bank 15, VCCO 3.3 V
set_property -dict {PACKAGE_PIN J20  IOSTANDARD LVCMOS33    } [get_ports aud_clk_44k]
set_property -dict {PACKAGE_PIN K18  IOSTANDARD LVCMOS33    } [get_ports aud_clk_48k]
set_property -dict {PACKAGE_PIN K13  IOSTANDARD LVCMOS33    } [get_ports bp_tdm_bclk]
set_property -dict {PACKAGE_PIN J17  IOSTANDARD LVCMOS33    } [get_ports bp_tdm_din]
set_property -dict {PACKAGE_PIN M13  IOSTANDARD LVCMOS33    } [get_ports bp_tdm_dout]
set_property -dict {PACKAGE_PIN L13  IOSTANDARD LVCMOS33    } [get_ports bp_tdm_fs]
set_property -dict {PACKAGE_PIN K14  IOSTANDARD LVCMOS33    } [get_ports bp_tdm_mclk]
set_property -dict {PACKAGE_PIN J22  IOSTANDARD LVCMOS33    } [get_ports fmc_a0]
set_property -dict {PACKAGE_PIN H18  IOSTANDARD LVCMOS33    } [get_ports fmc_a1]
set_property -dict {PACKAGE_PIN G13  IOSTANDARD LVCMOS33    } [get_ports fmc_a10]
set_property -dict {PACKAGE_PIN J16  IOSTANDARD LVCMOS33    } [get_ports fmc_a11]
set_property -dict {PACKAGE_PIN G17  IOSTANDARD LVCMOS33    } [get_ports fmc_a12]
set_property -dict {PACKAGE_PIN H22  IOSTANDARD LVCMOS33    } [get_ports fmc_a13]
set_property -dict {PACKAGE_PIN G18  IOSTANDARD LVCMOS33    } [get_ports fmc_a14]
set_property -dict {PACKAGE_PIN G20  IOSTANDARD LVCMOS33    } [get_ports fmc_a15]
set_property -dict {PACKAGE_PIN G15  IOSTANDARD LVCMOS33    } [get_ports fmc_a16]
set_property -dict {PACKAGE_PIN G16  IOSTANDARD LVCMOS33    } [get_ports fmc_a17]
set_property -dict {PACKAGE_PIN H20  IOSTANDARD LVCMOS33    } [get_ports fmc_a18]
set_property -dict {PACKAGE_PIN K22  IOSTANDARD LVCMOS33    } [get_ports fmc_a2]
set_property -dict {PACKAGE_PIN H17  IOSTANDARD LVCMOS33    } [get_ports fmc_a3]
set_property -dict {PACKAGE_PIN K21  IOSTANDARD LVCMOS33    } [get_ports fmc_a4]
set_property -dict {PACKAGE_PIN H15  IOSTANDARD LVCMOS33    } [get_ports fmc_a5]
set_property -dict {PACKAGE_PIN J14  IOSTANDARD LVCMOS33    } [get_ports fmc_a6]
set_property -dict {PACKAGE_PIN H13  IOSTANDARD LVCMOS33    } [get_ports fmc_a7]
set_property -dict {PACKAGE_PIN J15  IOSTANDARD LVCMOS33    } [get_ports fmc_a8]
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
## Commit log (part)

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2025-07-30 moving CAD files from signalmesh repo
2025-08-04 progress on creating APM board first
2025-08-20 progress on board sep
2025-08-29 replacing the nucleo part with generic headers!
2025-08-30 ready for fab?
2025-08-30 gerbers pt 1. part matching next
2025-08-30 jlcpcb files
2025-09-10 adding rev3 changes
2025-09-10 should be good for refab and actual layout. may need better BOM matching tho
2025-09-10 actually no. need to rework ADC lines and perhaps make a pinout to an adapter board for the potentiometers for control. could be 3-4 of them for now?
2025-09-11 gonna use a 10 pin FFC to connect to the actual peripheral board
2025-09-13 voltage divider
2025-09-13 this seems good enough
2025-09-14 uploaded to jlcpcb
2025-09-17 sent out for assembly
2025-09-22 starting 7sdd board
2025-09-24 hmmm
2025-09-26 readme update with mermaid diagram
2025-09-27 APM v3?
2025-09-28 more apm v3 edits. back to filter board?
2025-09-28 working on LPFs
2025-10-20 some changes needed for next version based on my recent testing on the new order. biggest issue is FFC connector seems off in routes, INA has bad pinouts?, and LEDs are bright as shit. should probabl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
2026-04-26 backups
2026-05-25 updating top v10. need to get 3v3 APM converged in schematic. routing is tricky right now. the components should be evenly laid out and have the NUCLEO pins be adjusted based on location
2026-05-26 i got orientation wrong big time
2026-05-26 more progress
2026-05-30 more routing
2026-06-13 ground planes on f and b cu
2026-06-14 getting APM V3 R1 made. starting R2
2026-06-15 fab v3 r2?
2026-06-15 saved fab files
2026-06-17 routed
2026-06-17 routing changes
2026-06-18 v4 with new FFC conn
2026-06-18 v4 routed with FPGA FMC
2026-06-22 adding APM v5 and ACM adapter board for 25K primer module
2026-06-22 trying to get ACM adpater board routed with debug USB C in absence of ofthe BL616C
2026-06-22 ACM module board routed
2026-06-23 add backside connector. fix front connector orientation
2026-06-23 figuring out FFC traces next
2026-06-25 getting ACM and APM schematics put together. tool for FMC pin mapping verif
2026-06-26 seems like everything is routed? off by 1 error for I2C FPGA pins fixed?
2026-06-26 adding renders and render script
2026-06-30 schematic for the oscillator board
2026-06-30 wiring things up
